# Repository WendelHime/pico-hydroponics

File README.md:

# pico-hydroponics

This project is under development, but basically it implements a script that connect to the internet through provided wi-fi credentials, collect metrics from pH4502c, dht22 and tds meter (pH, humidity, temperature, TDS and EC) and send the collected metrics to a cloud service.

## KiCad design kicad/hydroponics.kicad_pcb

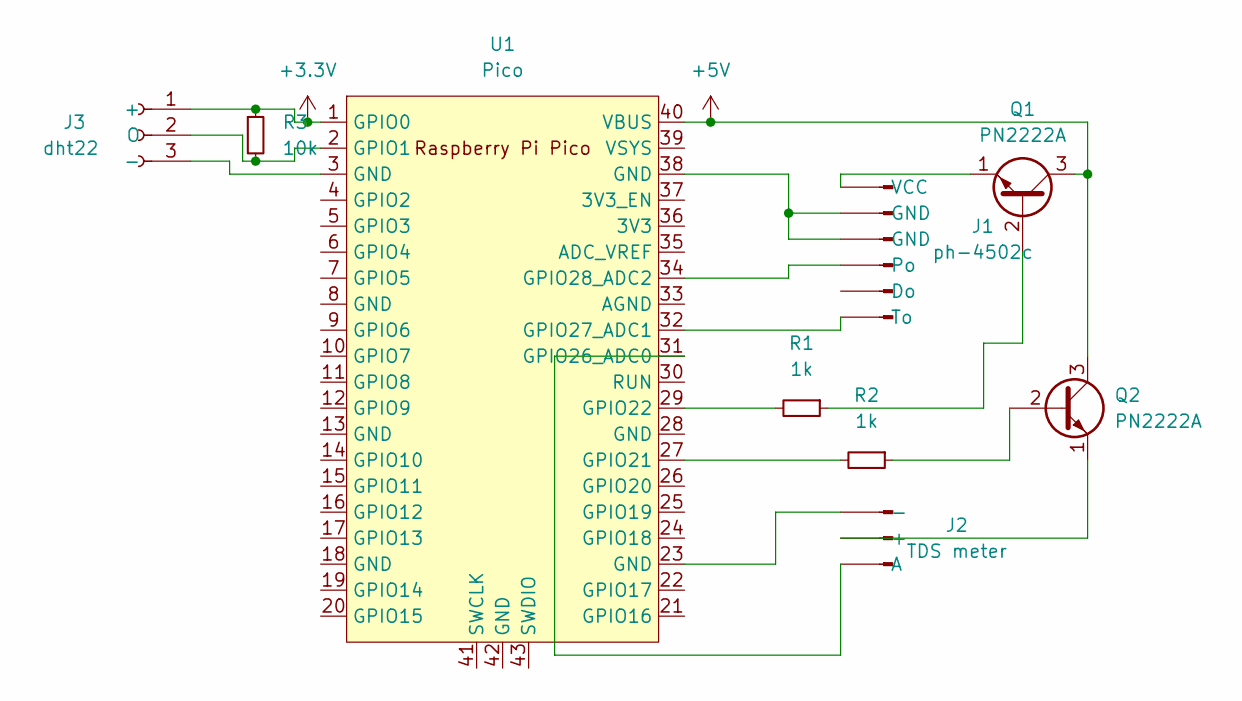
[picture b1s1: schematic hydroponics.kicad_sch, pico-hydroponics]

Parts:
J1: ph-4502c; PinHeader_1x06_P2.54mm_Vertical
J2: TDS meter; PinHeader_1x03_P2.54mm_Vertical
J3: dht22; PinSocket_1x03_P2.54mm_Vertical
Q1, Q2: PN2222A; TO-92_Inline
R1, R2: 1k; R_Axial_DIN0207_L6.3mm_D2.5mm_P2.54mm_Vertical
R3: 10k; R_Axial_DIN0207_L6.3mm_D2.5mm_P2.54mm_Vertical
U1: Pico; RPi_Pico_SMD_TH

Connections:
+3.3V: J3.1 (+), R3.1, U1.1 (GPIO0)
+5V: Q1.3 (C), Q2.3 (C), U1.40 (VBUS)
unnamed: J1.2 (GND), J1.3 (GND), U1.38 (GND)
unnamed: J1.4 (Po), U1.34 (GPIO28_ADC2)
unnamed: J1.6 (To), U1.32 (GPIO27_ADC1)
unnamed: J1.1 (VCC), Q1.1 (E)
unnamed: J2.2 (+), Q2.1 (E)
unnamed: J2.1 (-), U1.23 (GND)
unnamed: J2.3 (A), U1.31 (GPIO26_ADC0)
unnamed: J3.3 (-), U1.3 (GND)
unnamed: J3.2 (O), R3.2, U1.2 (GPIO1)
unnamed: Q1.2 (B), R1.1
unnamed: Q2.2 (B), R2.1
unnamed: R2.2, U1.27 (GPIO21)
unnamed: R1.2, U1.29 (GPIO22)

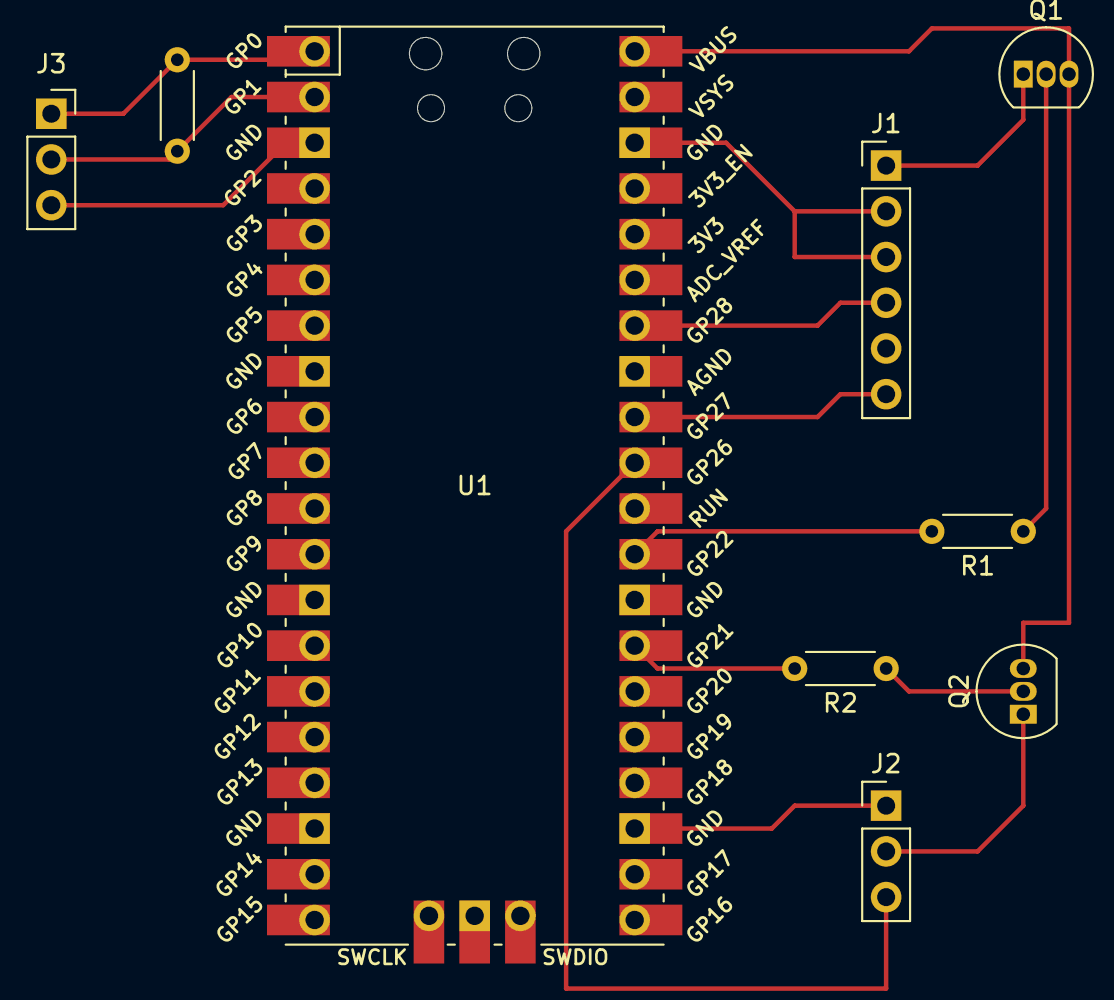
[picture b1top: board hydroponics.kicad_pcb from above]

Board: 2 copper layers, 9 parts (0 on the bottom side), 15 nets.

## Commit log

2023-07-09 add .gitignore
2023-07-09 add requirements.txt
2023-07-09 add main script
2023-07-09 add README.md
2023-07-13 request ntp for setting time; sending metrics to the service; updating linear regression equation for pH metric
2023-07-13 organize imports
2023-07-15 add transistor
2023-07-15 remove unused ntp code
2023-07-17 sleep betwen transistors and add ph temperature output
2023-07-19 chore: update gitignore
2023-07-19 chore: add kicad schematic and pcb
2023-07-19 feat: reduce time for collecting metrics and time for turning off and on sensors
2023-07-21 chore: update kicad design
2023-07-21 chore: update pin numbers
2023-07-21 feat: turn off ph after reading so we can economize some energy
2023-07-22 feat: break and organize modules
2023-07-22 feat: add microdot dependency to the project
2023-07-22 chore: update gitignore for ignoring secrets
2023-07-22 chore: update ph linear regression attributes names
2023-07-22 feat: add module for creating access point network
2023-07-22 feat: add HTTP server to be used during access point mode
2023-07-22 chore: remove secret dependency from std network module
2023-07-22 feat: add calibration logic
2023-07-22 feat: add ap mode server for calibration
2023-07-22 chore: update .gitignore
2023-07-29 feat: organize modules
2023-08-03 chore: add on kicad board settings and generate colored pcb ref and 3D image
